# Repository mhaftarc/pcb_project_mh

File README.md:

# STM32F446 Dev Board

PCB project for my PCB design course at university. The goal was to design a full board with a microcontroller, sensors, power supply and headers from scratch in KiCad, and to learn how to actually route a 2-layer board.

The board is based on the STM32F446RET6 (same MCU as on the Nucleo-F446RE I use) and is powered from USB-C.

## Pictures

Top layer:

Bottom layer:

Schematic: [plytkamh.pdf](docs/plytkamh.pdf)

## What's on the board

- STM32F446RET6 (LQFP64) with a 12 MHz crystal
- USB-C power input with ESD protection (USBLC6), PTC fuse and a reverse polarity diode
- 3.3 V LDO (LDL1117)
- BME280 - temperature, humidity and pressure sensor on I2C1
- TEMT6000 - ambient light sensor on the ADC (PA0)
- Power LED, status LED and 3 user LEDs
- RESET and USER buttons
- SWD header for programming (same pinout as CN4 on the Nucleo)
- BOOT0 jumper
- Two 2x10 headers for external stuff: COMM and ANALOG/GPIO

The board is 85 x 60 mm, 2 layers, with GND pours on both sides.

## What I used

- KiCad 10
- Freerouting
- STM32CubeMX (for checking the pin assignment)
- JLCPCB design rules
- Git

## Pinout

SWD (J3):

```
1  3V3
2  SWCLK (PA14)
3  GND
4  SWDIO (PA13)
5  NRST
6  SWO   (PB3)
```

COMM (J4):

```
 1  +3.3V              2  +5V
 3  GND                4  GND
 5  PC9                6  PA8
 7  PA9                8  PA10
 9  PA15              10  PC10
11  PC11              12  PC12
13  PD2               14  USART1_TX (PB6)
15  USART1_RX (PB7)   16  I2C1_SCL  (PB8)
17  I2C1_SDA  (PB9)   18  PC0
19  PC1               20  GND
```

ANALOG/GPIO (J5):

```
 1  +3.3V              2  GND
 3  SPI2_MOSI (PB15)   4  SPI2_MISO (PB14)
 5  SPI2_SCK  (PB13)   6  SPI2_NSS  (PB12)
 7  PB10               8  PB1
 9  PB0               10  PC5
11  PC4               12  PA7
13  PA6               14  PA4
15  USART2_RX (PA3)   16  USART2_TX (PA2)
17  PA1               18  PC3
19  PC2               20  GND
```

On-board stuff: BME280 on PB8/PB9, light sensor on PA0, status LED on PA5, user LEDs on PC6/PC7/PC8, user button on PC13.

USART1 is on PB6/PB7, not on the default PA9/PA10, so it has to be set that way in CubeMX.

## Project structure

```
plytkamh/
├── plytkamh.kicad_pro
├── plytkamh.kicad_sch
├── plytkamh.kicad_pcb
├── lib/        custom symbols/footprints (LDL1117, TEMT6000)
└── gerber/     files for the PCB manufacturer
```

## Notes

The first version of the board was 70 x 50 mm, but I couldn't fit all the header signals, so I made it bigger (85 x 60 mm).

At first the header pinout was done only in the schematic, without thinking about where the pins are on the MCU. During routing it turned out that half of the signals had to go around or under the whole chip. I changed the pinout so J4 gets the pins from the bottom side of the MCU and J5 from the top side, in the same order as on the package. After that the routing was much easier.

Power, USB, the crystal and all the decoupling capacitors were routed by hand. The rest of the GPIO lines going to the headers were routed with Freerouting and then cleaned up manually.

I also had a mistake in the schematic where the crystal wire was shorting PH1 with a few other pins. ERC didn't catch it because it was just one valid net, I found it when checking the netlist.

The BME280 is placed at the edge of the board, far from the LDO and the MCU, so it doesn't measure the heat from the board instead of the air.

## Status

Schematic and PCB are done, DRC is clean and the Gerber files are generated. The board hasn't been ordered or tested yet.

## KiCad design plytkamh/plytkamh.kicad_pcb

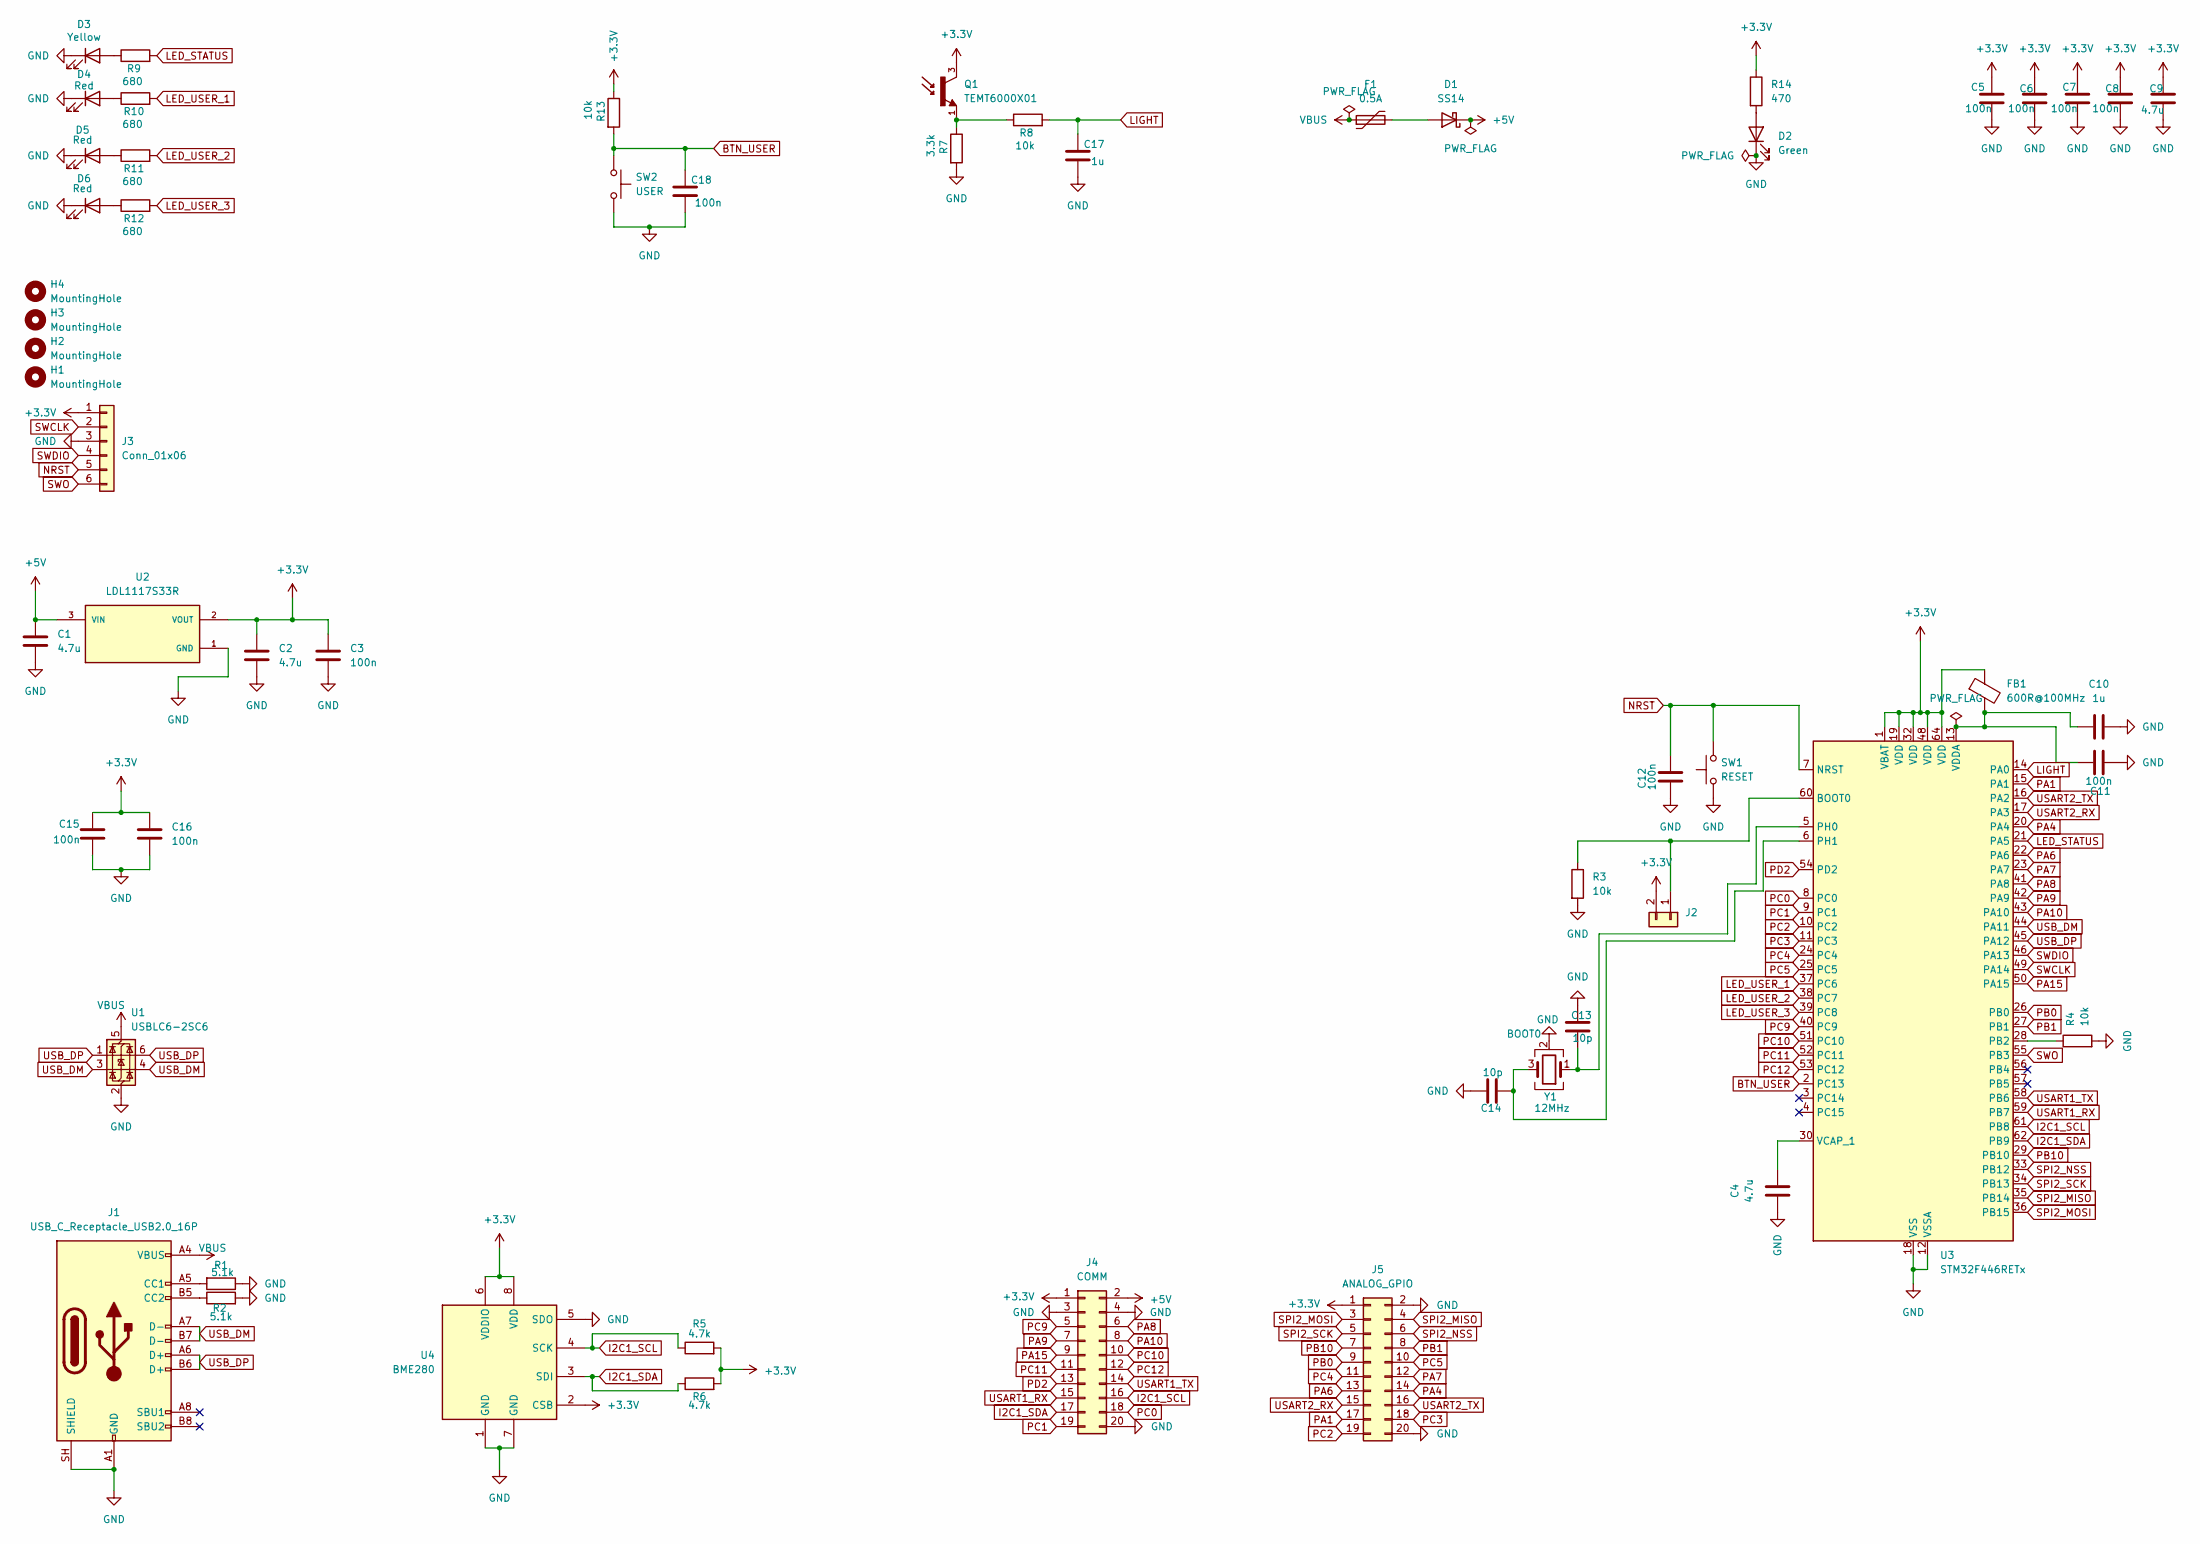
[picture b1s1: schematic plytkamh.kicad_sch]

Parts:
C1, C2, C4, C9: 4.7u; C_0603_1608Metric
C3, C5, C6, C7, C8, C11, C12, C15, C16, C18: 100n; C_0603_1608Metric
C10, C17: 1u; C_0603_1608Metric
C13, C14: 10p; C_0603_1608Metric
D1: SS14; D_SMA
D2: Green; LED_0603_1608Metric
D3: Yellow; LED_0603_1608Metric
D4, D5, D6: Red; LED_0603_1608Metric
F1: 0.5A; Fuse_1812_4532Metric
FB1: 600R@100MHz; L_0603_1608Metric
H1, H2, H3, H4: MountingHole; MountingHole_3.2mm_M3
J1: USB_C_Receptacle_USB2.0_16P; USB_C_Receptacle_GCT_USB4105-xx-A_16P_TopMnt_Horizontal
J2: BOOT0; PinHeader_1x02_P2.54mm_Vertical
J3: Conn_01x06; PinHeader_1x06_P2.54mm_Vertical
J4: COMM; PinHeader_2x10_P2.54mm_Vertical
J5: ANALOG_GPIO; PinHeader_2x10_P2.54mm_Vertical
Q1: TEMT6000X01; TRANS_TEMT6000X01; PARTREV 1.9
R1, R2: 5.1k; R_0603_1608Metric
R3, R4, R8, R13: 10k; R_0603_1608Metric
R5, R6: 4.7k; R_0603_1608Metric
R7: 3.3k; R_0603_1608Metric
R9, R10, R11, R12: 680; R_0603_1608Metric
R14: 470; R_0603_1608Metric
SW1: RESET; SW_PUSH_6mm
SW2: USER; SW_PUSH_6mm
U1: USBLC6-2SC6; SOT-23-6
U2: LDL1117S33R; SOT-223; PARTREV 7
U3: STM32F446RETx; LQFP-64_10x10mm_P0.5mm
U4: BME280; Bosch_LGA-8_2.5x2.5mm_P0.65mm_ClockwisePinNumbering
Y1: 12MHz; Crystal_SMD_3225-4Pin_3.2x2.5mm

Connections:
+3.3V: C2.1, C3.1, C5.1, C6.1, C7.1, C8.1, C9.1, C15.2, C16.2, FB1.1, J2.2, J3.1, J4.1, J5.1, Q1.3, R5.2, R6.2, R13.1, R14.1, U2.2 (VOUT), U2.4 (VOUT), U3.1 (VBAT), U3.19 (VDD), U3.32 (VDD), U3.48 (VDD), U3.64 (VDD), U4.2 (CSB), U4.6 (VDDIO), U4.8 (VDD)
+5V: C1.1, D1.1 (K), J4.2, U2.3 (VIN)
BTN_USER: C18.1, R13.2, SW2.1, U3.2 (PC13)
GND: C1.2, C2.2, C3.2, C4.1, C5.2, C6.2, C7.2, C8.2, C9.2, C10.2, C11.2, C12.2, C13.2, C14.2, C15.1, C16.1, C17.2, C18.2, D2.1 (K), D3.1 (K), D4.1 (K), D5.1 (K), D6.1 (K), J1.A1 (GND), J1.A12 (GND), J1.B1 (GND), J1.B12 (GND), J1.SH (SHIELD), J3.3, J4.3, J4.4, J4.20, J5.2, J5.20, R1.1, R2.2, R3.2, R4.2, R7.2, SW1.1, SW2.2, U1.2 (GND), U2.1 (GND), U3.12 (VSSA), U3.18 (VSS), U3.31 (VSS), U3.47 (VSS), U3.63 (VSS), U4.1 (GND), U4.5 (SDO), U4.7 (GND), Y1.2 (G), Y1.4 (G)
I2C1_SCL: J4.16, R5.1, U3.61 (PB8), U4.4 (SCK)
I2C1_SDA: J4.17, R6.1, U3.62 (PB9), U4.3 (SDI)
LED_STATUS: R9.2, U3.21 (PA5)
LED_USER_1: R10.2, U3.37 (PC6)
LED_USER_2: R11.2, U3.38 (PC7)
LED_USER_3: R12.2, U3.39 (PC8)
LIGHT: C17.1, R8.2, U3.14 (PA0)
NRST: C12.1, J3.5, SW1.2, U3.7 (NRST)
unnamed: D1.2 (A), F1.2
unnamed: D2.2 (A), R14.2
unnamed: D3.2 (A), R9.1
unnamed: D4.2 (A), R10.1
unnamed: D5.2 (A), R11.1
unnamed: D6.2 (A), R12.1
unnamed: J1.A5 (CC1), R1.2
unnamed: J1.B5 (CC2), R2.1
unnamed: J2.1, R3.1, U3.60 (BOOT0)
unnamed: Q1.1, R7.1, R8.1
unnamed: R4.1, U3.28 (PB2)
unnamed: C13.1, U3.5 (PH0), Y1.1
unnamed: C14.1, U3.6 (PH1), Y1.3
unnamed: C4.2, U3.30 (VCAP_1)
unnamed: C10.1, C11.1, FB1.2, U3.13 (VDDA)
PA1: J5.17, U3.15 (PA1)
PA4: J5.14, U3.20 (PA4)
PA6: J5.13, U3.22 (PA6)
PA7: J5.12, U3.23 (PA7)
PA8: J4.6, U3.41 (PA8)
PA9: J4.7, U3.42 (PA9)
PA10: J4.8, U3.43 (PA10)
PA15: J4.9, U3.50 (PA15)
PB0: J5.9, U3.26 (PB0)
PB1: J5.8, U3.27 (PB1)
PB10: J5.7, U3.29 (PB10)
PC0: J4.18, U3.8 (PC0)
PC1: J4.19, U3.9 (PC1)
PC2: J5.19, U3.10 (PC2)
PC3: J5.18, U3.11 (PC3)
PC4: J5.11, U3.24 (PC4)
PC5: J5.10, U3.25 (PC5)
PC9: J4.5, U3.40 (PC9)
PC10: J4.10, U3.51 (PC10)
PC11: J4.11, U3.52 (PC11)
PC12: J4.12, U3.53 (PC12)
PD2: J4.13, U3.54 (PD2)
SPI2_MISO: J5.4, U3.35 (PB14)
SPI2_MOSI: J5.3, U3.36 (PB15)
SPI2_NSS: J5.6, U3.33 (PB12)
SPI2_SCK: J5.5, U3.34 (PB13)
SWCLK: J3.2, U3.49 (PA14)
SWDIO: J3.4, U3.46 (PA13)
SWO: J3.6, U3.55 (PB3)
USART1_RX: J4.15, U3.59 (PB7)
USART1_TX: J4.14, U3.58 (PB6)
USART2_RX: J5.15, U3.17 (PA3)
USART2_TX: J5.16, U3.16 (PA2)
USB_DM: J1.A7 (D-), J1.B7 (D-), U1.3 (I/O2), U1.4 (I/O2), U3.44 (PA11)
USB_DP: J1.A6 (D+), J1.B6 (D+), U1.1 (I/O1), U1.6 (I/O1), U3.45 (PA12)
VBUS: F1.1, J1.A4 (VBUS), J1.A9 (VBUS), J1.B4 (VBUS), J1.B9 (VBUS), U1.5 (VBUS)

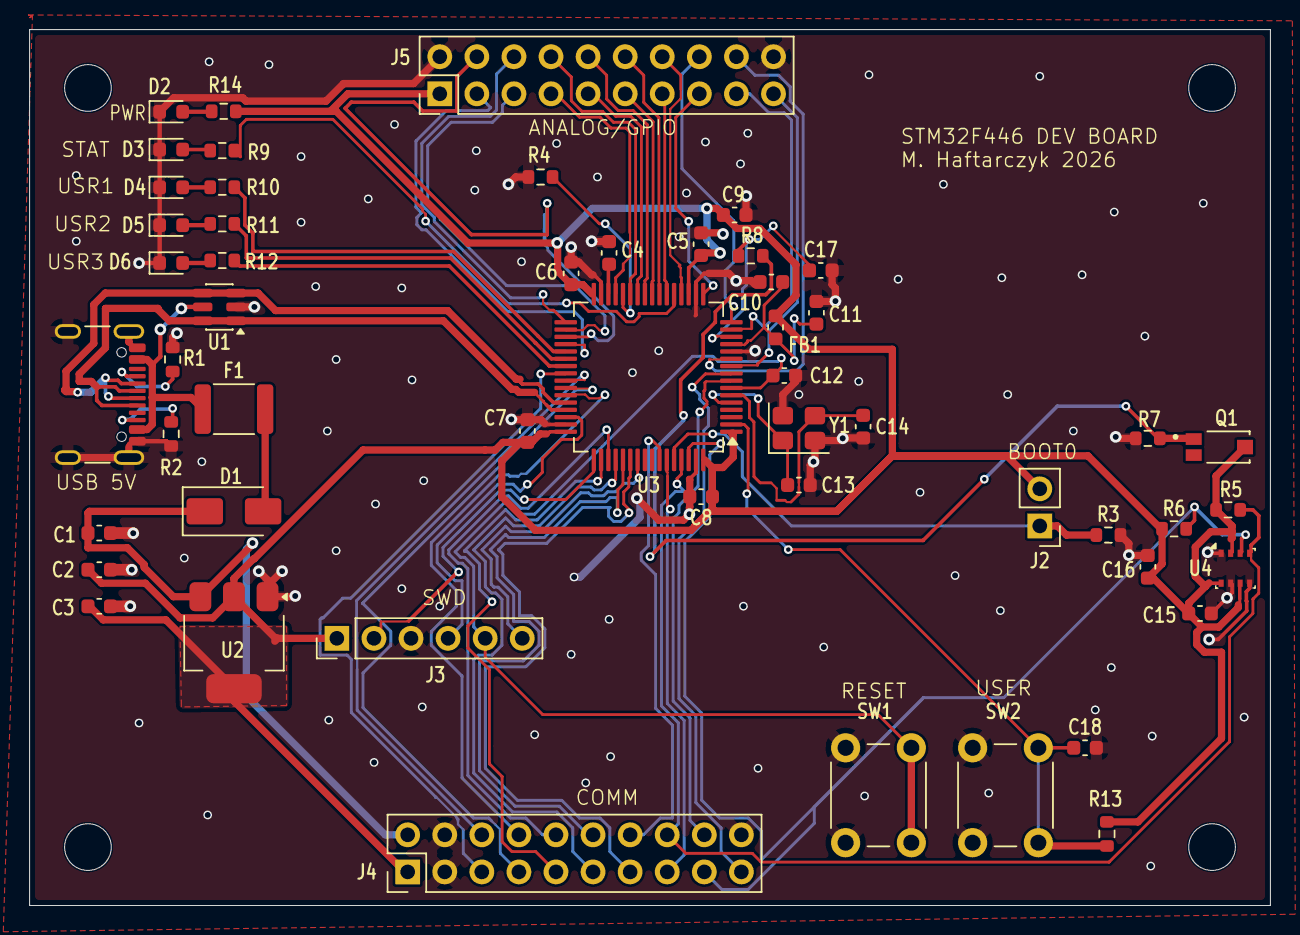
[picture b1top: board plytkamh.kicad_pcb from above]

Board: 2 copper layers, 85.0 x 60.0 mm, 57 parts (0 on the bottom side), 63 nets.
